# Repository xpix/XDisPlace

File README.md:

# XDisPlace
XDisplace are a complete solution to mill, dispense solder paste and pixk and place components to a pcb in one process!

I made a long video playlist to explain all my steps to develop this Feature. Please watch it:

A nice explain why XDisPlace exists from this website: http://nerdclub-uk.blogspot.de/2016/06/sacrificing-pins-to-make-pcb-layout.html

Wherever possible, we like to try to keep to single-sided boards, even for designs going "into production". While it's easy to throw together a poorly-designed, double-sided PCB and send it off to a factory to get made up, that means delays and waiting; and quite often, a much slower development cycle - particularly if, like us, you have an iterative design process!

Keeping designs to single-sides means you can knock up some ferric chloride, try out your design and have a working board in hours, not days or even weeks.

But even if your project isn't time sensitive and you can afford to wait weeks, between ordering and receiving your boards, it often means either:

a) when the board needs redesigning (because you forgot to include the ground plane, or re-route that pin you left a "to-do" note against and then ignored - don't pretend it hasn't happened) you've got another four-to-six-week wait while the new boards arrive OR

b) tack-soldering a few wires and slicing traces with a craft knife, just to get the thing up and working.

Either way, you end up with a less-than ideal PCB or weeks and months of delays.
Homebrew etching is ugly. The results are less than perfect. It's messy and you'll stain your hands yellow for days (and possibly the sink forever if you're not careful). But it gets a result - quickly.

So if you need to redesign a board, you can simply print out a new design, slap down some toner transfer, whack it in some ferric chloride and an hour or two later, you've an amended design. And once you're absolutely sure your design works, you can send the exact same PCB layout to your favourite factory/fab-house and then wait (one time only) for the nice, shiny, silk-screened-and-solder-masked versions to arrive, for the final product.

That's why we still make our own PCBs.
It might not be fashionable (in fact there are plenty people who ask why, when having PCBs manufactured is so cheap, would you want to still etch your own boards) but it is quick and allows the iterative design process to complete fully - no boards with bits of wires tacked on because we've committed to a single design now (even with faults/errors) and can't wait any longer to get the thing soldered up and tested! That's why we favour single-sided designs.

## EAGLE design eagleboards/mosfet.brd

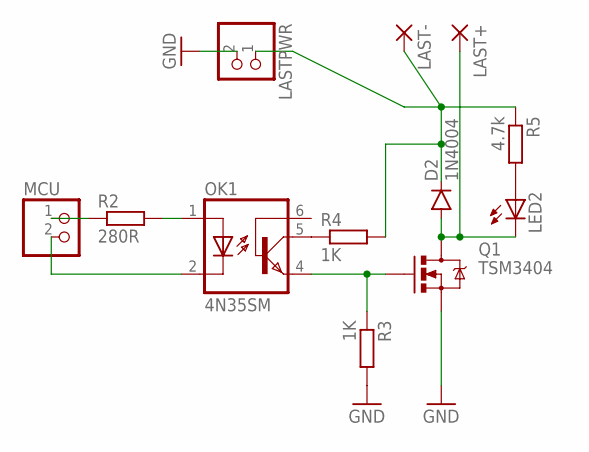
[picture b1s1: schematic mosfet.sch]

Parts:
D2: 1N4004; SOD-123
LAST+: WIREPADSMD2,54-5,08; SMD2,54-5,08
LAST-: WIREPADSMD2,54-5,08; SMD2,54-5,08
LASTPWR: PINHD-1X2; 1X02
LED2: LEDCHIP-LED0805; CHIP-LED0805
MCU: PINHD-1X2; 1X02
OK1: 4N35SM; DIL6-SMD
Q1: TSM3404; SOT23-3
R2: 280R; R0805
R3, R4: 1K; R0805
R5: 4.7k; R0805

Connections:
GND: LASTPWR.2, Q1.2 (S), R3.2
LAST+: D2.C, LAST-.1, LASTPWR.1, R4.2, R5.1
LAST-: D2.A, LAST+.1, LED2.C, Q1.3 (D)
unnamed: OK1.1 (A), R2.2
unnamed: MCU.1, R2.1
unnamed: MCU.2, OK1.2 (C)
unnamed: OK1.4 (EMI), Q1.1 (G), R3.1
unnamed: OK1.5 (COL), R4.1
unnamed: LED2.A, R5.2

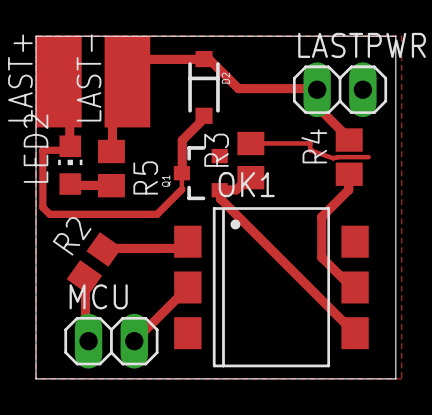
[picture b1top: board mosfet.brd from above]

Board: 2 copper layers, 20.0 x 19.0 mm, 12 parts (0 on the bottom side), 9 nets.

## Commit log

2015-11-21 :neckbeard: Added .gitattributes & .gitignore files
2015-11-21 Initialize Project
2015-11-27 add the press and release for pivot in macro add new commands for this 'start' and 'stop' change drop parameters in example gcode add persistence for parameter at dispenser code
2015-11-30 - use only split to get infos about the pause command
2015-12-01 - add calibrate gcode
2015-12-01 imporove calibrate code for dispenser
2015-12-01 - remove spacing in result gcode
2015-12-01 - add some generated gcode
2015-12-02 - add a nice library for exists canulla with there color gode and inside diameters
2015-12-14 - add dispenser widget - add onoholder cambam project - add camera widget
2015-12-14 - add some fixes to last stable dispenser widget
2015-12-14 - remove stepsfordrop - add save options to local space
2015-12-15 - organize gcode in parts of an array to put later gcode from widgets - add some methods for this
2015-12-15 - add initial flow informations
2016-02-08 - new files - some changes
2016-02-10 - remove obsolete files
2016-02-10 - new cmabam files for Holder at cnc 3040 - new cambam file for platform
2017-05-10 Saved IDEAS.md with Dillinger.io [skip ci]
2017-05-12 Saved IDEAS.md with Dillinger.io

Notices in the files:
parts and their libraries:
SparkFun-DiscreteSemi: Licensing: Creative Commons ShareAlike 4.0 International - https://creativecommons.org/licenses/by-sa/4.0
